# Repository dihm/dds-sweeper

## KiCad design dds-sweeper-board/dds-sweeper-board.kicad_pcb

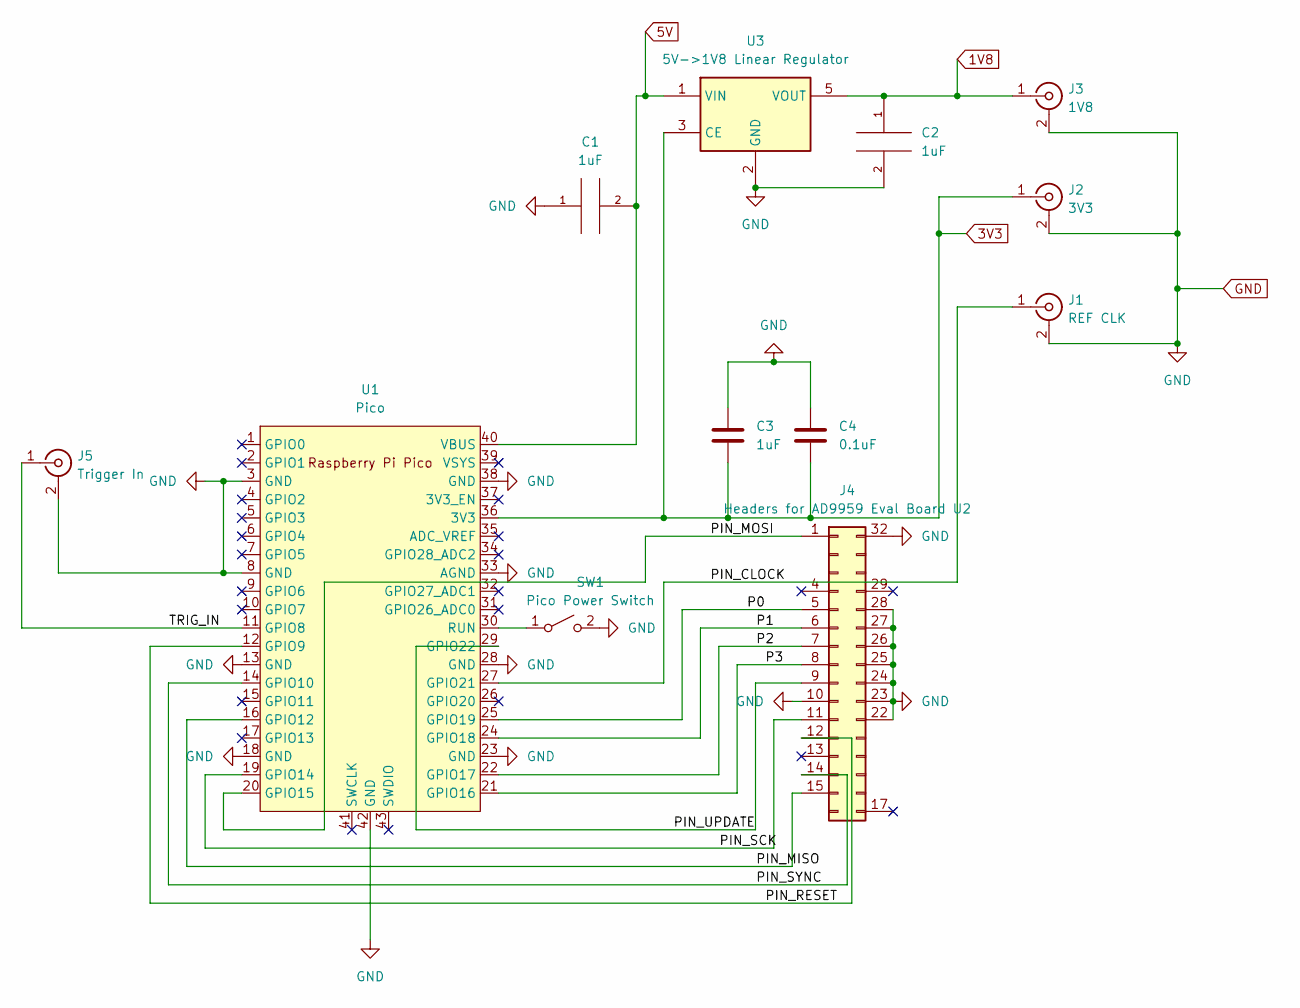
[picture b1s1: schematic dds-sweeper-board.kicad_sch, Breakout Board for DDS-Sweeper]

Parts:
C1, C2, C3: 1uF; C_0805_2012Metric_Pad1.18x1.45mm_HandSolder
C4: 0.1uF; C_0805_2012Metric_Pad1.18x1.45mm_HandSolder
J1: REF CLK; SMA_Samtec_SMA-J-P-X-ST-EM1_EdgeMount
J2: 3V3; SMA_Samtec_SMA-J-P-X-ST-EM1_EdgeMount
J3: 1V8; SMA_Samtec_SMA-J-P-X-ST-EM1_EdgeMount
J4: Headers for AD9959 Eval Board U2; PinSocket_2x16_P2.54mm_Vertical_DDS_Sweeper
J5: Trigger In; SMA_Samtec_SMA-J-P-X-ST-EM1_EdgeMount
SW1: Pico Power Switch; PinSocket_1x03_P2.54mm_Vertical
U1: Pico; RPi_Pico_SMD
U3: 5V->1V8 Linear Regulator; SOT-23-5

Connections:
1V8: C2.1, J3.1 (In), U3.5 (VOUT)
3V3: C3.2, C4.2, J2.1 (In), U1.36 (3V3), U3.3 (CE)
5V: C1.2, U1.40 (VBUS), U3.1 (VIN)
/P0: J4.5, U1.25 (GPIO19)
/P1: J4.6, U1.24 (GPIO18)
/P2: J4.7, U1.22 (GPIO17)
/P3: J4.8, U1.21 (GPIO16)
/PIN_CLOCK: J1.1 (In), U1.27 (GPIO21)
/PIN_MISO: J4.15, U1.16 (GPIO12)
/PIN_MOSI: J4.1, U1.20 (GPIO15)
/PIN_RESET: J4.12, U1.12 (GPIO9)
/PIN_SCK: J4.11, U1.19 (GPIO14)
/PIN_SYNC: J4.14, U1.14 (GPIO10)
/PIN_UPDATE: J4.9, U1.29 (GPIO22)
/TRIG_IN: J5.1 (In), U1.11 (GPIO8)
GND: C1.1, C2.2, C3.1, C4.1, J1.2 (Ext), J2.2 (Ext), J3.2 (Ext), J4.10, J4.22, J4.23, J4.24, J4.25, J4.26, J4.27, J4.28, J4.32, J5.2 (Ext), SW1.2 (B), U1.3 (GND), U1.8 (GND), U1.13 (GND), U1.18 (GND), U1.23 (GND), U1.28 (GND), U1.33 (AGND), U1.38 (GND), U1.42 (GND), U3.2 (GND)
unnamed: SW1.1 (A), U1.30 (RUN)

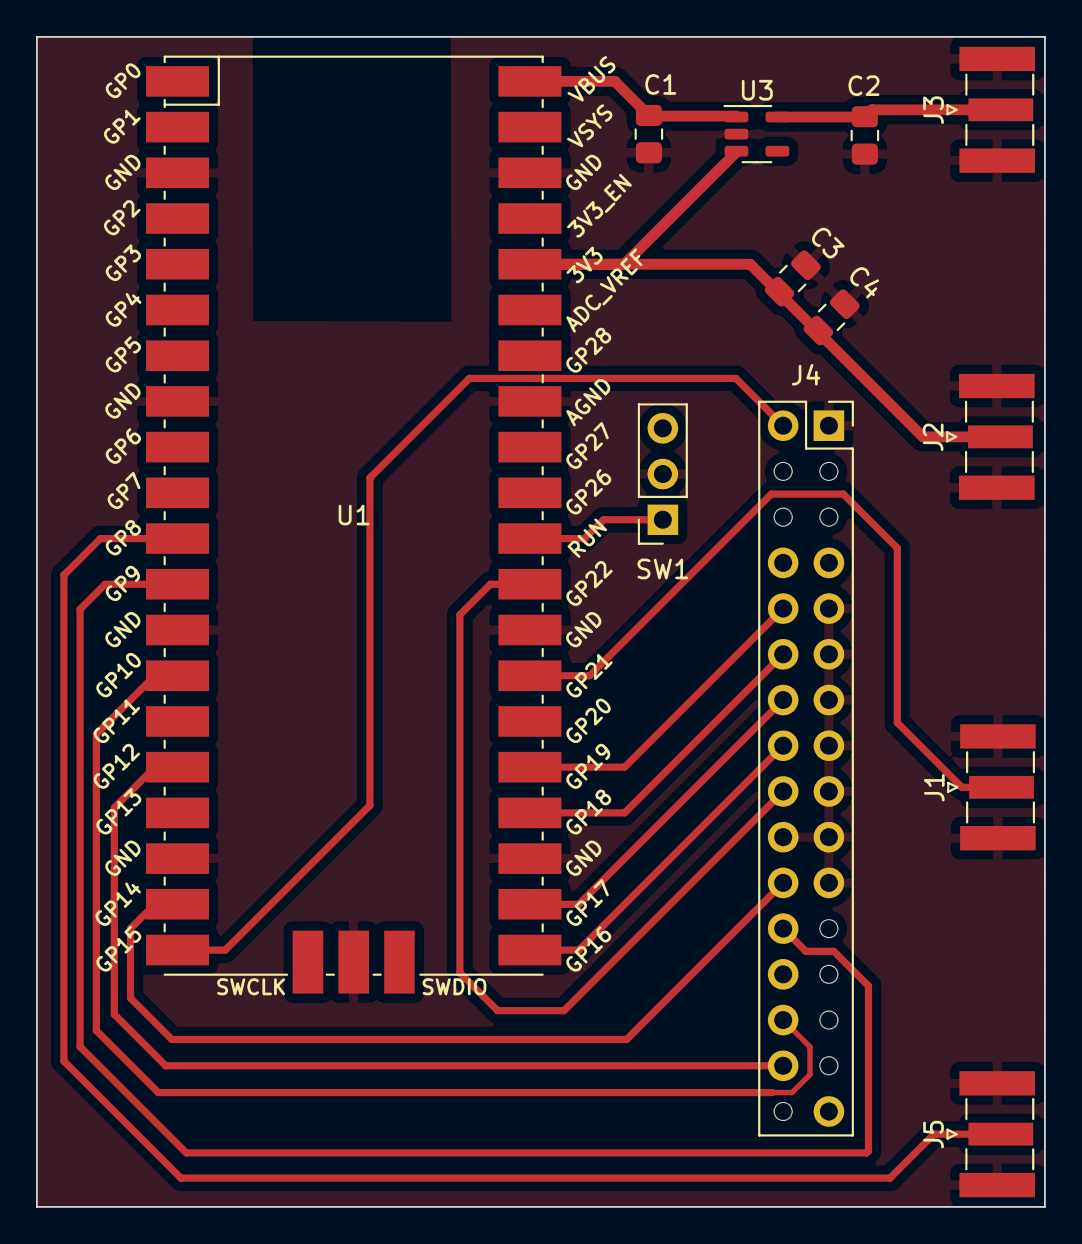
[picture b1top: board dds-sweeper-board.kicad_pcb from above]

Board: 2 copper layers, 56.0 x 65.0 mm, 12 parts (0 on the bottom side), 17 nets.

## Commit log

2024-10-04 Minor tweaks to the breakout board.
    Adds filter capacitors to the 3.3V line.
    Tweaks some KiCAD options to suppress errors and warnings.
    Added labels to lines going to the AD9959
